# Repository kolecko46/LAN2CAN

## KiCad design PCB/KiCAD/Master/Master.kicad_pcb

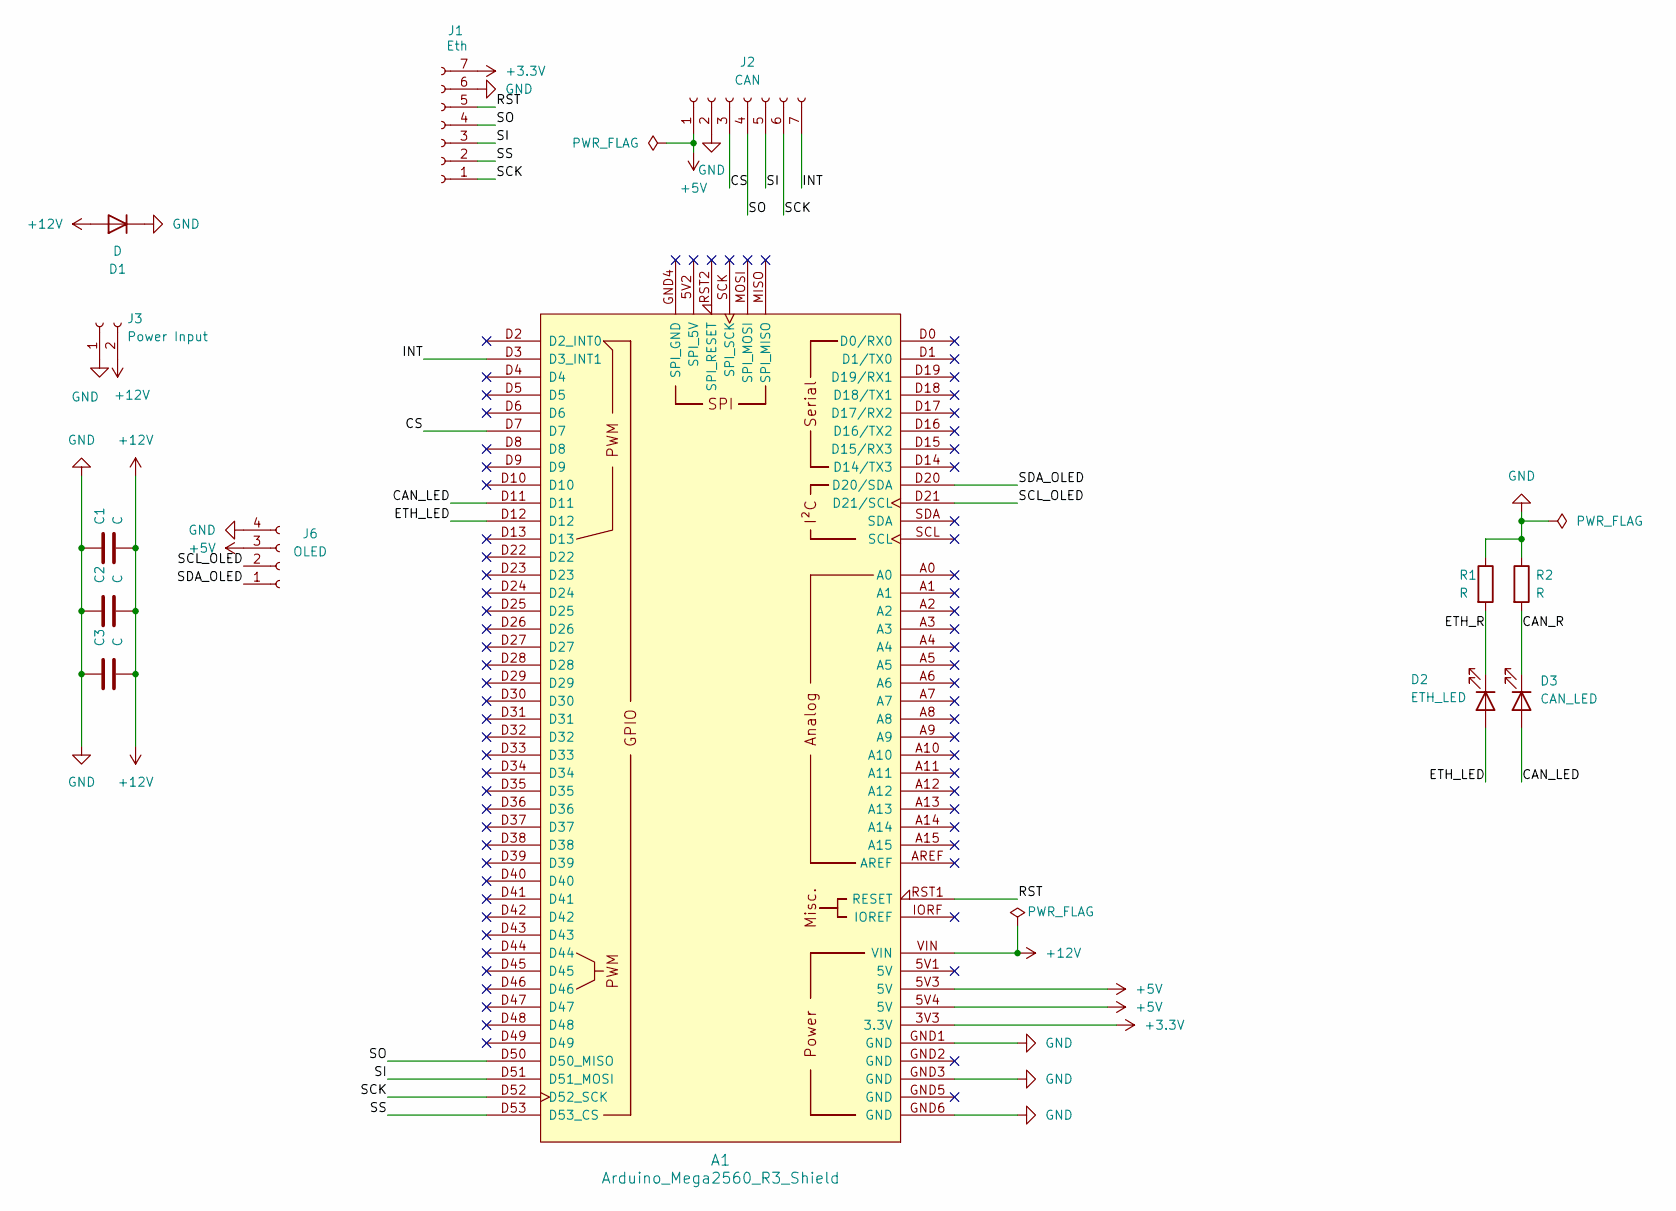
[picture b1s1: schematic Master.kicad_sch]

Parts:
A1: Arduino_Mega2560_R3_Shield
C1, C2, C3: C; C_0805_2012Metric_Pad1.18x1.45mm_HandSolder
D1: D; D_0805_2012Metric_Pad1.15x1.40mm_HandSolder
D2: ETH_LED; LED_0805_2012Metric_Pad1.15x1.40mm_HandSolder
D3: CAN_LED; LED_0805_2012Metric_Pad1.15x1.40mm_HandSolder
J1: Eth; JST_XH_B7B-XH-AM_1x07_P2.50mm_Vertical
J2: CAN; JST_XH_B7B-XH-AM_1x07_P2.50mm_Vertical
J3: Power Input; JST_XH_B2B-XH-A_1x02_P2.50mm_Vertical
J6: OLED; JST_XH_B4B-XH-A_1x04_P2.50mm_Vertical
R1, R2: R; R_0805_2012Metric_Pad1.20x1.40mm_HandSolder

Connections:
+3.3V: A1.3V3 (3.3V), J1.7
+5V: A1.5V3 (5V), A1.5V4 (5V), J2.1, J6.3
+12V: A1.VIN, C1.2, C2.2, C3.2, D1.2 (A), J3.2
/CAN_LED: A1.D11, D3.2 (A)
/CAN_R: D3.1 (K), R2.2
/CS: A1.D7, J2.3
/ETH_LED: A1.D12, D2.2 (A)
/ETH_R: D2.1 (K), R1.2
/INT: A1.D3 (D3_INT1), J2.7
/RST: A1.RST1 (RESET), J1.5
/SCK: A1.D52 (D52_SCK), J1.1, J2.6
/SCL_OLED: A1.D21 (D21/SCL), J6.2
/SDA_OLED: A1.D20 (D20/SDA), J6.1
/SI: A1.D51 (D51_MOSI), J1.3, J2.5
/SO: A1.D50 (D50_MISO), J1.4, J2.4
/SS: A1.D53 (D53_CS), J1.2
GND: A1.GND1 (GND), A1.GND3 (GND), A1.GND6 (GND), C1.1, C2.1, C3.1, D1.1 (K), J1.6, J2.2, J3.1, J6.4, R1.1, R2.1

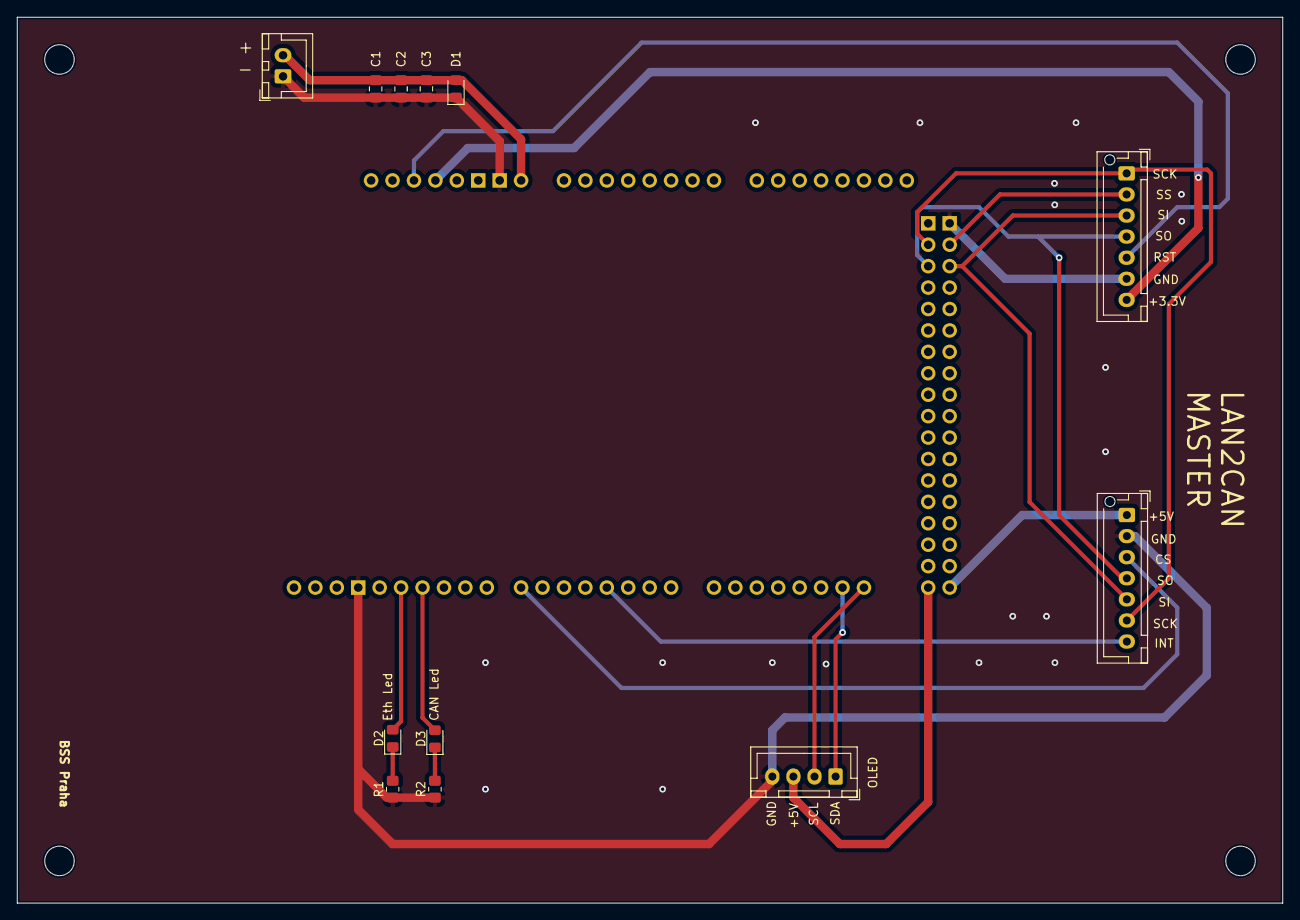
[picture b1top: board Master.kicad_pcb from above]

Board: 2 copper layers, 150.0 x 105.0 mm, 13 parts (0 on the bottom side), 17 nets.

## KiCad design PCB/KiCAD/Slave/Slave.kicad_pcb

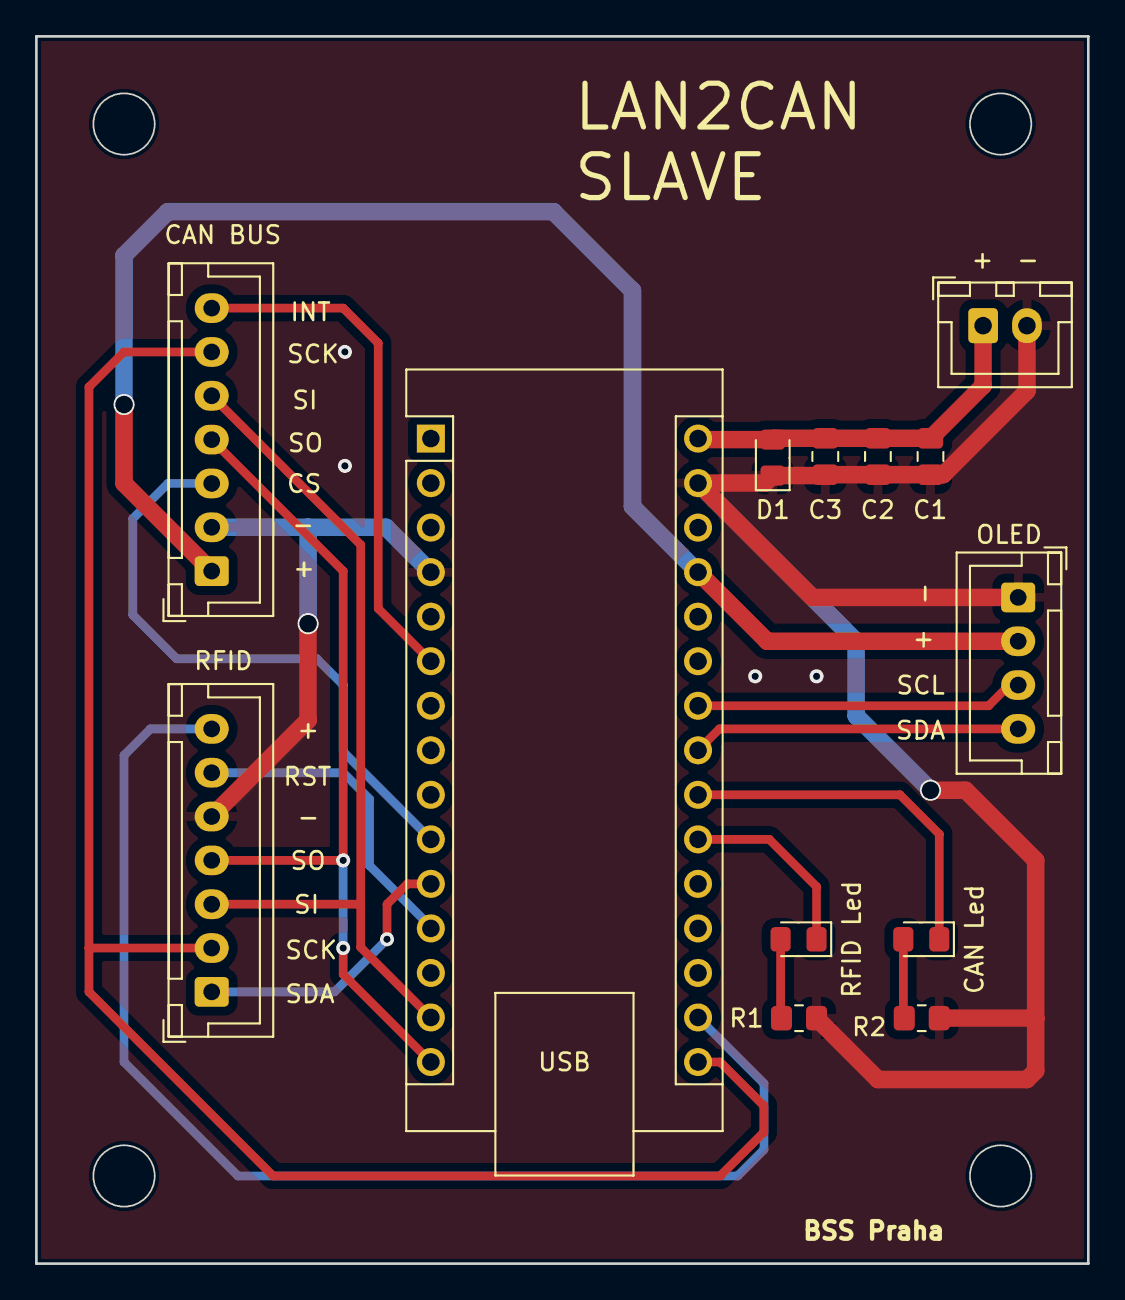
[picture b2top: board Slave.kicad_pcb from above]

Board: 2 copper layers, 60.0 x 70.0 mm, 13 parts (0 on the bottom side), 17 nets.

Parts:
A1: Arduino_Nano_v3.x; Arduino_Nano
C1, C2, C3: C; C_0805_2012Metric_Pad1.18x1.45mm_HandSolder
CAN Led: LED; LED_0805_2012Metric_Pad1.15x1.40mm_HandSolder
D1: TVS DIODA; D_0805_2012Metric_Pad1.15x1.40mm_HandSolder
J1: RFID; JST_XH_B7B-XH-A_1x07_P2.50mm_Vertical
J2: Power; JST_XH_B2B-XH-A_1x02_P2.50mm_Vertical
J3: CAN_BUS; JST_XH_B7B-XH-A_1x07_P2.50mm_Vertical
J6: I2C_Display; JST_XH_B4B-XH-A_1x04_P2.50mm_Vertical
R1, R2: 330R; R_0805_2012Metric_Pad1.20x1.40mm_HandSolder
RFID Led: LED; LED_0805_2012Metric_Pad1.15x1.40mm_HandSolder

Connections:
+3.3V: A1.17 (3V3), J1.7
+5V: A1.27 (+5V), J3.1, J6.2
+12V: A1.30 (VIN), C1.1, C2.1, C3.1, D1.2 (A), J2.1
/CAN_LED: A1.22 (A3), CAN Led.1 (K)
/CAN_R: CAN Led.2 (A), R2.2
/CS: A1.10 (D7), J3.3
/INT: A1.6 (D3), J3.7
/RFID_LED: A1.21 (A2), RFID Led.1 (K)
/RFID_R: R1.1, RFID Led.2 (A)
/RST: A1.12 (D9), J1.6
/SCK: A1.16 (D13), J1.2, J3.6
/SCL_OLED: A1.24 (A5), J6.3
/SDA: A1.11 (D8), J1.1
/SDA_OLED: A1.23 (A4), J6.4
/SI: A1.14 (D11), J1.3, J3.5
/SO: A1.15 (D12), J1.4, J3.4
GND: A1.4 (GND), A1.29 (GND), C1.2, C2.2, C3.2, D1.1 (K), J1.5, J2.2, J3.2, J6.1, R1.2, R2.1
